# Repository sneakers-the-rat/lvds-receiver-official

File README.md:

# Photodiode LVDS Receiver — 50 Mbps optical receiver module

Replacement for the SiPM-based receiver (Hamamatsu C15522-3010SA module) used for the
optical uplink in Miniscope Zero (Sasatani et al., bioRxiv 2026.09.05.745822).

Design target (set by the customer, not taken from the paper):
- 50 Mbps line rate, 8b/10b coding, 40 Mbps payload, UI = 20 ns
- The paper's mode, as transmitted: Manchester-coded 8 Mbps data (16 Mbaud)
- Optical in (630 nm red / 740 nm NIR channels of the paper), LVDS out (TIA/EIA-644)
- USB-programmable and USB-verifiable from any laptop, no FPGA, no programmer dongle
- Detector: linear-mode Si APD (SiPM rejected: see docs/02-architecture.md)

Status board, stage log and test results: docs/00-status.md
Requirements derived from the paper: docs/01-requirements.md
Architecture and part selection: docs/02-architecture.md
Link budget / noise calculations: sim/link_budget.py (outputs results/link_budget.txt)
Simulations: sim/ (ngspice + Python, each with a pass/fail check)
Firmware: firmware/ (STM32H723 + USB3300 USB-HS, CDC + vendor bulk)
Host tool: host/ (Python, pyusb/serial, PRBS + 8b/10b + Manchester verify)
Hardware: hw/ (KiCad 7 project, generated fabrication outputs in hw/fab/)

Clean-room statement: this design was written from the paper, manufacturer
datasheets (in datasheets/) and first-principles calculations only. No existing
KiCad project was consulted or copied.

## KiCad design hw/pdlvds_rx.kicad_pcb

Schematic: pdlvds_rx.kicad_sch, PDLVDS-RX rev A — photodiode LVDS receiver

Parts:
C1: 0.4pF NP0; C_0402_1005Metric
C2, C3, C7, C8, C9, C10, C11, C13, C14, C16, C19, C23, C26, C27, C30, C47, C48, C50: 100nF; C_0603_1608Metric
C4: 1uF 630V ECWFD2J105JB; ECWFD_1uF_630V
C5, C34: 1nF; C_0603_1608Metric
C6, C25, C35, C37, C51: 10uF; C_0805_2012Metric
C12: 1uF; C_0603_1608Metric
C15: 0.47uF; C_0603_1608Metric
C17, C18: 2.2uF; C_0603_1608Metric
C20: 33pF; C_0402_1005Metric
C21: 33pF; C_0603_1608Metric
C22: 4.7uF; C_0402_1005Metric
C24, C28: 100nF; C_0402_1005Metric
C29: 10nF; C_0603_1608Metric
C31: 4.7uF 10V CL10J475KP8N3NC; C_0603_1608Metric
C32, C33, C52, C53, C54: 100nF 630V; C_1206_3216Metric
C36, C39: 3.3nF; C_0603_1608Metric
C38, C40, C41: 22uF; C_0805_2012Metric
C42, C43, C44, C45, C46, C49: 4.7uF; C_0603_1608Metric
CL1, CL2, CL3, CL4, CL5: Harwin S1001-46R shield clip; HARWIN_S1001
D1: C30737LH-500-90; C30737LH_LCC6
D2: S8664-20K (DNP alt); S8664_TO5
D3: USBLC6-2SC6; SOT-23-6
D4: SMBJ5.0A; D_SMB
D6: LED green PWR; LED_0603_1608Metric
D7: LED green STAT; LED_0603_1608Metric
D8: SMT740 740nm LED BIST source; SMT740_3227
D9: SMBJ5384B 160V OVP DNP (S8664 fit); D_SMB
D10, D11: SMBJ5383B 150V OVP DNP (S8664 fit); D_SMB
D12, D13, D14, D15: ES1J; D_SMA
F1: PTC 1.1A; Fuse_1812_4532Metric
FB1: BLM21PG601SN1D 600R 1.4A; L_0805_2012Metric
FB2: BLM21SP601SN1D 600R 2.3A; L_0805_2012Metric
J1: USB-C receptacle; USB_C_Receptacle_Amphenol_12401610E4-2A
J2: LVDS out 2x3; PinHeader_2x03_P2.54mm_Vertical
J3: SMA test in; SMA_Amphenol_132134_Vertical
J4: SWD 2x5 1.27; PinHeader_2x05_P1.27mm_Vertical
J5: HV enable jumper; PinHeader_1x02_P2.54mm_Vertical
L1: 2.2uH DFE201612E-2R2M=P2 Isat2.4A; L_Murata_DFE201610P
L2: 2.2uH DFE201612E-2R2M=P2; L_Murata_DFE201610P
MH1, MH2, MH3, MH4: M3 corner; MountingHole_3.2mm_M3
MH5, MH6: M2.5 lens holder; MountingHole_2.7mm_M2.5
Q1: IRLML0060TRPBF; SOT-23
R1: 3.3k; R_0603_1608Metric
R2, R10, R44, R45: 1k; R_0603_1608Metric
R3: 806R; R_0603_1608Metric
R4: 200R; R_0603_1608Metric
R5, R6, R12, R15, R16, R22, R23, R37: 10k; R_0603_1608Metric
R7: 0R (fit for TIA direct); R_0603_1608Metric
R8: 0R DNP (fit for post-amp); R_0603_1608Metric
R9: 100k (hysteresis); R_0603_1608Metric
R11: 49.9R DNP; R_0603_1608Metric
R13, R14, R46: 100R; R_0603_1608Metric
R17: 12k 1%; R_0603_1608Metric
R18, R19: 5.1k; R_0603_1608Metric
R20, R21: 4.7k; R_0603_1608Metric
R24: 53.6k (RT, f=250kHz per LT3757 Table 1); R_0603_1608Metric
R25: 143k; R_0603_1608Metric
R26: 33k; R_0603_1608Metric
R27: 10R; R_0603_1608Metric
R28: 0.15R; R_1206_3216Metric
R29: 5.00k HV73V1J (1 of 2); R_0603_1608Metric
R30: 2.35M HV73V2B bleeder (1 of 2); R_1206_3216Metric
R31: 2.94M 0.1% TNPV1210 divider top (1 of 3); R_1210_3225Metric
R32: 75.0k 0.1%; R_0603_1608Metric
R33: 140k 0.1% DAC inject; R_0603_1608Metric
R34: 10M HV73V2B; R_1206_3216Metric
R35: 312k; R_0603_1608Metric
R36, R39: 100k; R_0603_1608Metric
R38: 587k; R_0603_1608Metric
R40: 46k RSET=+4.6V; R_0603_1608Metric
R41, R43: 1k ILIM=125mA; R_0603_1608Metric
R42: 33.2k RSET=+3.32V; R_0603_1608Metric
R47: 5.00k HV73V1J (2 of 2); R_0603_1608Metric
R48: 2.35M HV73V2B bleeder (2 of 2); R_1206_3216Metric
R49: 2.37M 0.1% TNPV1210 divider top (2 of 3); R_1210_3225Metric
R50: 2.37M 0.1% TNPV1210 divider top (3 of 3); R_1210_3225Metric
RJ1, RJ2: 0R DNP; R_0603_1608Metric
SH1: Harwin S02-20150300 20x15x3 can (S1001-46R clips); SHIELD_CAN_S02_20150300
T1: Wurth WE-FLEX HV 749196518 1:5 (N1 pri, N2-N6 sec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; WEFLEXHV_EFD20_12
TP1: HV test point; TestPoint_Pad_D1.5mm
TP2: DBG TX test point; TestPoint_Pad_D1.5mm
TP3: DBG RX test point; TestPoint_Pad_D1.5mm
U1: OPA657N; SOIC-8_3.9x4.9mm_P1.27mm
U2: THS4304DBV; SOT-23-5
U3: LMH7220MK; TSOT-23-6
U4: ADN2813ACPZ; QFN-32-1EP_5x5mm_P0.5mm_EP3.1x3.1mm
U5: SN65LVDS32D; SOIC-16_3.9x9.9mm_P1.27mm
U6: STM32H723ZGT6; LQFP-144_20x20mm_P0.5mm
U7: USB3300-EZK; QFN-32-1EP_5x5mm_P0.5mm_EP3.1x3.1mm
U8: DAC8562SDGS; VSSOP-10_3x3mm_P0.5mm
U9: TMP117NAI; TMP117_WSON6
U10: LT3757EMSE; MSOP-10-1EP_3x3mm_P0.5mm_EP1.68x1.88mm
U11: TPS62130RGT; QFN-16-1EP_3x3mm_P0.5mm_EP1.45x1.45mm
U12: TPS62130RGT (inv); QFN-16-1EP_3x3mm_P0.5mm_EP1.45x1.45mm
U13: LT3042EDD (+VA); DFN-10-1EP_3x3mm_P0.5mm_EP1.55x2.48mm
U14: LT3042EDD (+3V3A); DFN-10-1EP_3x3mm_P0.5mm_EP1.55x2.48mm
X1: 24.000MHz ECS-240-20-5PDN-TR CL20; Crystal_SMD_HC49-SD
X2: ASE-25.000MHZ-L-R-T 3.3V CMOS OSC; Oscillator_SMD_Abracon_ASE-4Pin_3.2x2.5mm

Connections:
+3V3A: C24.1, C46.1, C49.1, U6.32 (VREF+), U6.33 (VDDA), U7.6 (VDD3.3), U7.16 (VDD3.3), U7.25 (VDD3.3), U7.30 (VDD3.3), U7.31 (REG_EN), U9.5 (V+), U14.9 (OUTS), U14.10 (OUT)
+3V3D: C16.1, C27.1, C28.1, C38.1, C47.1, C48.1, D6.2 (A), FB1.1, J4.1 (VTREF), L1.2, R15.2, R20.2, R21.2, R22.2, R35.1, R37.2, R45.1, R46.1, U5.4 (G), U5.10 (3A), U5.14 (4A), U5.16 (VCC), U6.6 (VBAT), U6.17 (VDD), U6.30 (VDD), U6.39 (VDD), U6.52 (VDD), U6.62 (VDD), U6.72 (VDD), U6.84 (VDD), U6.108 (VDD), U6.121 (VDD), U6.131 (VDD), U6.143 (PDR_ON), U6.144 (VDD), U8.5 (CLR), U8.9 (AVDD), U11.14 (VOS), X2.1 (OE), X2.4 (VCC)
+3V3D_CDR: C50.1, C51.1, FB1.2, U4.1 (VCC), U4.2 (VCC), U4.12 (VCC), U4.18 (VCC), U4.24 (VCC), U4.31 (VCC), U4.32 (VCC)
+5V: C25.1, C35.1, C37.1, C43.1, D3.5 (VBUS), D4.1 (K), F1.2, R25.1, T1.1 (PRI_A), U7.4 (VBUS), U10.10 (VIN), U11.10 (AVIN), U11.11 (PVIN), U11.12 (PVIN), U11.13 (EN), U12.10 (AVIN), U12.11 (PVIN), U12.12 (PVIN), U12.13 (EN), U13.1 (IN), U13.2 (IN), U13.3 (EN/UV), U13.6 (PGFB), U14.1 (IN), U14.2 (IN), U14.3 (EN/UV), U14.6 (PGFB)
+VA: C2.1, C7.1, C10.1, C44.1, R5.1, U1.7 (V+), U2.5 (VS+), U3.5 (VCC), U13.9 (OUTS), U13.10 (OUT)
-VA: C3.1, C41.1, FB2.2, U1.4 (V-)
APD_A: C1.2, D1.1 (ANODE), D1.2 (ANODE), D1.3 (ANODE), D1.4 (ANODE), D1.6 (ANODE), R1.2, RJ1.2, U1.2 (-IN)
APD_A_ALT: D2.1 (LEAD_A), RJ1.1
APD_K: C4.1, C33.1, D1.5 (CATHODE), R30.1, R31.1, R34.1, R47.2, RJ2.2
APD_K_ALT: D2.2 (LEAD_K), RJ2.1
BIST_A: D8.2 (A), R46.2
BIST_DRV: D8.1 (K), U6.98 (PC8)
BOOT0: R16.1, U6.138 (BOOT0)
CAP_CLK: U5.5 (2Y), U6.34 (PA0)
CAP_DATA: U5.3 (1Y), U6.35 (PA1)
CC1: J1.A5 (CC1), R18.1
CC2: J1.B5 (CC2), R19.1
CDR_CLKN: J2.6 (CLKN), R14.2, U4.25 (CLKOUTN), U5.7 (2B)
CDR_CLKP: J2.5 (CLKP), R14.1, U4.26 (CLKOUTP), U5.6 (2A)
CDR_DATN: J2.2 (DATN), R13.2, U4.28 (DATAOUTN), U5.1 (1B)
CDR_DATP: J2.1 (DATP), R13.1, U4.29 (DATAOUTP), U5.2 (1A)
CDR_LOL: U4.16 (LOL), U6.36 (PA2)
CDR_LOS: U4.22 (LOS), U6.75 (PB14)
CDR_NIN: C9.2, U4.4 (NIN)
CDR_PIN: C8.2, U4.5 (PIN)
CDR_SQUELCH: U4.27 (SQUELCH), U6.76 (PB15)
CDR_VREF: C12.1, U4.3 (VREF)
CF1: C15.1, U4.15 (CF1)
CF2: C15.2, U4.14 (CF2)
CMP_IN: R7.2, R8.2, R9.2, R11.2, U3.6 (IN+)
CMP_QN: C9.1, U3.3 (Qn)
CMP_QP: C8.1, R9.1, U3.4 (Q)
DAC_SYNC: U6.110 (PA15(JTDI)), U8.6 (SYNC)
DAC_VREF: C26.1, U8.10 (VREF)
DBG_RX: TP3.1, U6.102 (PA10)
DBG_TX: TP2.1, U6.101 (PA9)
DM_CON: D3.3 (IO2), J1.A7 (DN), J1.B7 (DN)
DM_PHY: D3.4 (IO2p), U7.8 (DM)
DP_CON: D3.1 (IO1), J1.A6 (DP), J1.B6 (DP)
DP_PHY: D3.6 (IO1p), U7.7 (DP)
FB_3V3: R35.2, R36.1, U11.5 (FB)
FB_NEG: R38.2, R39.1, U12.5 (FB)
FLY_PRI: Q1.3 (D), T1.2 (PRI_B)
GND: C2.2, C3.2, C4.2, C6.2, C7.2, C10.2, C11.2, C12.2, C14.2, C16.2, C17.2, C18.2, C19.2, C20.2, C21.2, C22.2, C23.2, C24.2, C25.2, C26.2, C27.2, C28.2, C29.2, C30.2, C31.2, C32.2, C33.2, C34.2, C35.2, C36.2, C37.2, C38.2, C40.1, C41.2, C42.2, C43.2, C44.2, C45.2, C46.2, C47.2, C48.2, C49.2, C50.2, C51.2, C53.2, CL1.1, CL1.2, CL1.3, CL2.1, CL2.2, CL2.3, CL3.1, CL3.2, CL3.3, CL4.1, CL4.2, CL4.3, CL5.1, CL5.2, CL5.3, D2.3 (CASE), D3.2 (GND), D4.2 (A), D11.2 (A), D12.2 (A), J1.A1 (GND), J1.A12 (GND), J1.B1 (GND), J1.B12 (GND), J1.SH (SHIELD), J2.3 (GND), J2.4 (GND), J3.2 (SH), J3.3 (SH), J3.4 (SH), J3.5 (SH), J4.3 (GND), J4.5 (GND), J4.7 (GND), J4.9 (GND), MH1.1, MH2.1, MH3.1, MH4.1, R6.2, R12.2, R16.2, R17.2, R18.2, R19.2, R24.2, R26.2, R28.2, R32.2, R36.2, R38.1, R40.2, R41.2, R42.2, R43.2, R44.2, R48.2, T1.3 (SEC_GND), U1.3 (+IN), U2.2 (VS-), U3.2 (GND), U4.8 (VEE), U4.13 (VEE), U4.17 (VEE), U4.19 (SADDR5), U4.23 (VEE), U4.30 (VEE), U4.33 (EP), U5.8 (GND), U5.9 (3B), U5.12 (Gn), U5.15 (4B), U6.16 (VSS), U6.31 (VSSA), U6.38 (VSS), U6.51 (VSS), U6.61 (VSS), U6.83 (VSS), U6.94 (VSS), U6.107 (VSS), U6.120 (VSS), U6.130 (VSS), U7.1 (GND), U7.2 (GND), U7.5 (ID), U7.10 (EXTVBUS), U7.33 (EP), U8.3 (GND), U8.4 (LDAC), U9.2 (GND), U9.4 (ADD0), U9.7 (EP), U10.5 (SYNC), U10.11 (EP), U11.6 (AGND), U11.7 (FSW), U11.8 (DEF), U11.15 (PGND), U11.16 (PGND), U11.17 (EP), U13.8 (GND), U13.11 (EP), U14.8 (GND), U14.11 (EP), X2.2 (GND)
HV_DAC: R33.1, U8.2 (VOUTB)
HV_EN: J5.1 (EN), U6.97 (PC7)
HV_FBX: C34.1, R32.1, R33.2, R50.2, U10.2 (FBX)
HV_GATE: R27.1, U10.7 (GATE)
HV_INTVCC: C31.1, U10.8 (INTVCC)
HV_M1: C52.2, C54.1, D12.1 (K), D13.2 (A)
HV_M2: C53.1, D13.1 (K), D14.2 (A)
HV_M3: C54.2, D14.1 (K), D15.2 (A)
HV_OVP1: D9.2 (A), D10.1 (K)
HV_OVP2: D10.2 (A), D11.1 (K)
HV_R29M: R29.2, R47.1
HV_R30M: R30.2, R48.1
HV_R31A: R31.2, R49.1
HV_R31B: R49.2, R50.1
HV_RAW: C32.1, D9.1 (K), D15.1 (K), R29.1
HV_RT: R24.1, U10.4 (RT)
HV_S1: T1.4 (S1), T1.5 (S1B)
HV_S2: T1.6 (S2), T1.12 (S2B)
HV_S3: T1.10 (S3B), T1.11 (S3)
HV_S4: T1.8 (S4B), T1.9 (S4)
HV_SEC: C52.1, T1.7 (SEC_A)
HV_SENSE: Q1.2 (S), R28.1, U10.6 (SENSE)
HV_SHDN: J5.2 (SHDN), R25.2, R26.1, U6.42 (PA6), U10.9 (SHDN/UVLO)
HV_SS: C30.1, U10.3 (SS)
HV_VC: R23.1, U10.1 (VC)
HV_VC2: C29.1, R23.2
I2C_SCL: R20.1, U4.20 (SCK), U6.136 (PB6), U9.1 (SCL)
I2C_SDA: R21.1, U4.21 (SDA), U6.137 (PB7), U9.6 (SDA)
ILIM_A: R43.1, U14.5 (ILIM)
ILIM_P: R41.1, U13.5 (ILIM)
LED_PWR_K: D6.1 (K), R44.1
LED_STAT: D7.1 (K), U6.99 (PC9)
LED_STAT_A: D7.2 (A), R45.2
MOS_G: Q1.1 (G), R27.2
NEG_RAW: C39.2, C40.2, FB2.1, L2.2, R39.2, U12.6 (AGND), U12.7 (FSW), U12.8 (DEF), U12.14 (VOS), U12.15 (PGND), U12.16 (PGND), U12.17 (EP)
NRST: C19.1, J4.10 (NRST), R15.1, U6.25 (NRST)
PG_3V3: R37.1, U6.140 (PB9), U11.4 (PG)
PHY_1V8: C22.1, U7.15 (VDD1.8), U7.26 (VDD1.8)
PHY_1V8A: C23.1, U7.29 (VDDA1.8)
POST_INN: R3.2, R4.1, U2.4 (IN-)
POST_INP: C5.2, R2.1, U2.3 (IN+)
POST_OUT: R3.1, R8.1, U2.1 (VOUT)
RBIAS: R17.1, U7.32 (RBIAS)
REFCLK: U4.10 (REFCLKP), X2.3 (OUT)
REFCLKN: C14.1, U4.11 (REFCLKN)
SET_A: C45.1, R42.1, U14.7 (SET)
SET_P: C42.1, R40.1, U13.7 (SET)
SLICEN: C13.2, U4.7 (SLICEN)
SLICEP: C13.1, U4.6 (SLICEP)
SPI_MOSI: U6.113 (PC12), U8.8 (DIN)
SPI_SCK: U6.111 (PC10), U8.7 (SCLK)
SS_3V3: C36.1, U11.9 (SS/TR)
SS_NEG: C39.1, U12.9 (SS/TR)
SW1: L1.1, U11.1 (SW), U11.2 (SW), U11.3 (SW)
SW2: L2.1, U12.1 (SW), U12.2 (SW), U12.3 (SW)
SWCLK: J4.4 (SWCLK), U6.109 (PA14(JTCK)
SWDIO: J4.2 (SWDIO), U6.105 (PA13(JTMS)
TEST_IN: J3.1 (SIG), R11.1
THRADJ: R12.1, U4.9 (THRADJ)
THR_DAC: R10.1, U8.1 (VOUTA)
THR_FILT: C11.1, R10.2, U3.1 (IN-)
TIA_OUT: C1.1, C5.1, R1.1, R7.1, U1.6 (OUT)
TMP_ALERT: R22.1, U6.139 (PB8), U9.3 (ALERT)
TP_HV: R34.2, TP1.1
ULPI_CK: U6.41 (PA5), U7.14 (CLKOUT)
ULPI_D0: U6.37 (PA3), U7.24 (DATA0)
ULPI_D1: U6.46 (PB0), U7.23 (DATA1)
ULPI_D2: U6.47 (PB1), U7.22 (DATA2)
ULPI_D3: U6.69 (PB10), U7.21 (DATA3)
ULPI_D4: U6.70 (PB11), U7.20 (DATA4)
ULPI_D5: U6.73 (PB12), U7.19 (DATA5)
ULPI_D6: U6.74 (PB13), U7.18 (DATA6)
ULPI_D7: U6.135 (PB5), U7.17 (DATA7)
ULPI_DIR: U6.28 (PC2_C), U7.12 (DIR)
ULPI_NXT: U6.29 (PC3_C), U7.11 (NXT)
ULPI_STP: U6.26 (PC0), U7.13 (STP)
USB_RST: U6.40 (PA4), U7.9 (RESET)
VBUS_RAW: F1.1, J1.A4 (VBUS), J1.A9 (VBUS), J1.B4 (VBUS), J1.B9 (VBUS)
VCAP1: C17.1, U6.106 (VCAP)
VCAP2: C18.1, U6.71 (VCAP)
VMID: C6.1, R2.2, R4.2, R5.2, R6.1
XI: C20.1, U7.28 (XI), X1.1 (XI)
XO: C21.1, U7.27 (XO), X1.2 (XO)

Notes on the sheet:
ANALOG FRONT END - APD / TIA / COMPARATOR
HV BIAS - LT3757 FLYBACK
POWER - BUCKS + LDOs
CLOCK + DATA RECOVERY - ADN2813
MCU - STM32H723
USB - USB3300 PHY + USB-C
MECHANICAL
LVDS -> CMOS CAPTURE + LVDS OUTPUT
DAC + TEMPERATURE - DAC8562 / TMP117
LEDS / MISC

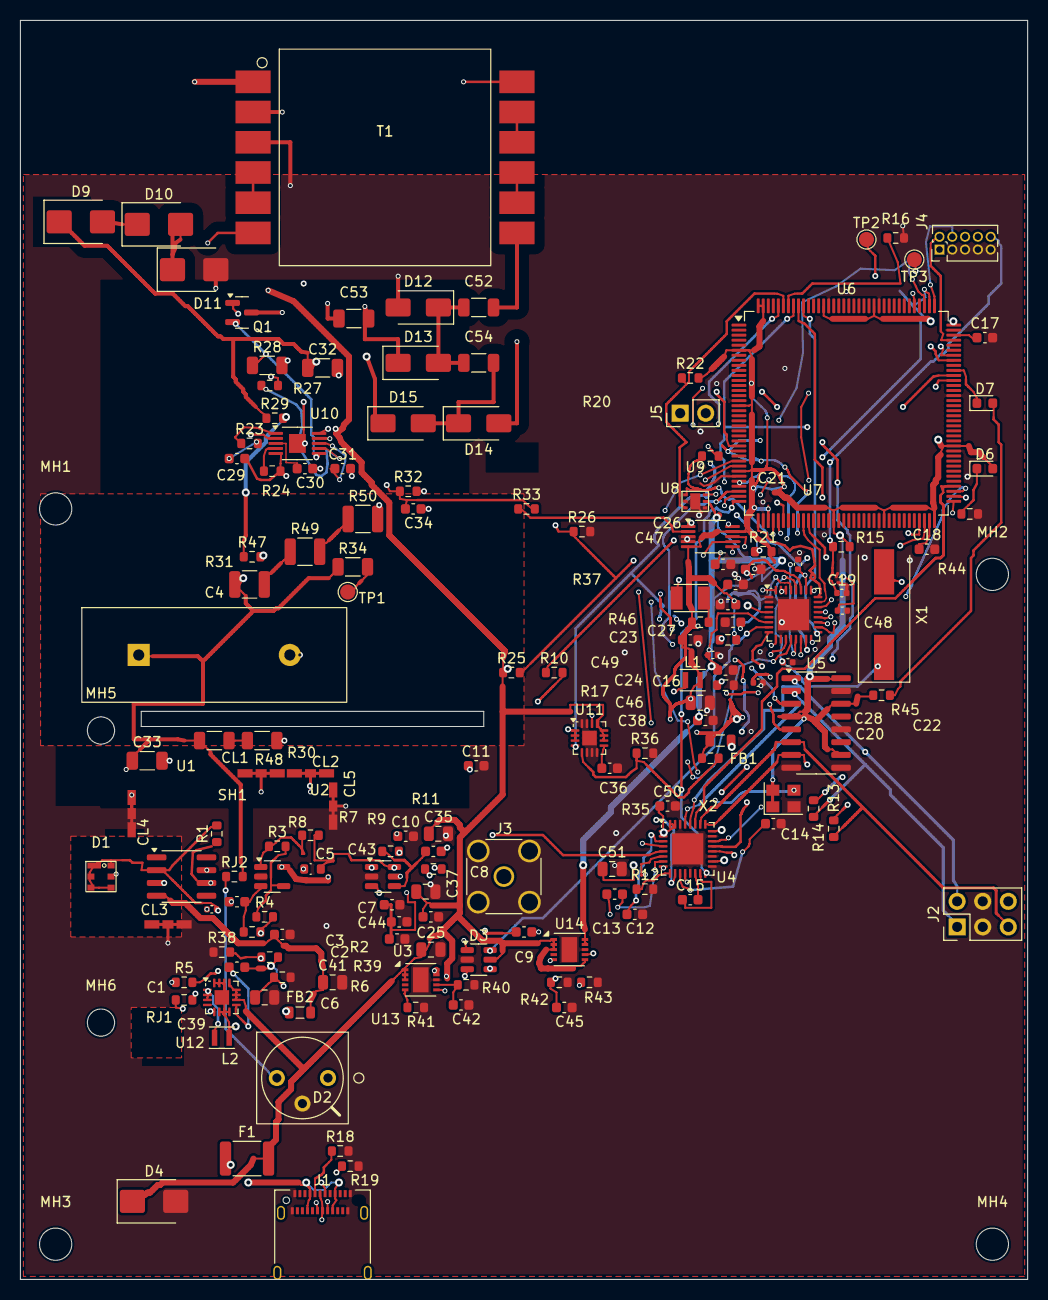
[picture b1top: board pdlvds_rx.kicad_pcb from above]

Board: 4 copper layers, 100.0 x 125.0 mm, 163 parts (1 on the bottom side), 127 nets.

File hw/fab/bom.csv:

Refs,Qty,Value,Footprint
C1,1,0.4pF NP0,Capacitor_SMD:C_0402_1005Metric
C15,1,0.47uF,Capacitor_SMD:C_0603_1608Metric
C17 C18,2,2.2uF,Capacitor_SMD:C_0603_1608Metric
C2 C3 C7 C8 C9 C10 C11 C13 C14 C16 C19 C23 C24 C26 C27 C28 C30 C47 C48 C50,20,100nF,Capacitor_SMD:C_0603_1608Metric
C20 C21,2,18pF,Capacitor_SMD:C_0603_1608Metric
C22 C31 C42 C43 C44 C45 C46 C49,8,4.7uF,Capacitor_SMD:C_0603_1608Metric
C29,1,10nF,Capacitor_SMD:C_0603_1608Metric
C32 C33,2,100nF 630V,Capacitor_SMD:C_1206_3216Metric
C36 C39,2,3.3nF,Capacitor_SMD:C_0603_1608Metric
C38 C40 C41,3,22uF,Capacitor_SMD:C_0805_2012Metric
C4 C12,2,1uF,Capacitor_SMD:C_0603_1608Metric
C5 C34,2,1nF,Capacitor_SMD:C_0603_1608Metric
C6 C25 C35 C37 C51,5,10uF,Capacitor_SMD:C_0805_2012Metric
D1,1,C30737LH-500-90,pdlvds:C30737LH_LCC6
D2,1,S8664-20K (DNP alt),pdlvds:S8664_TO5
D3,1,USBLC6-2SC6,Package_TO_SOT_SMD:SOT-23-6
D4,1,SMBJ5.0A,Diode_SMD:D_SMA
D5,1,ES1J,Diode_SMD:D_SMA
D6,1,LED green PWR,LED_SMD:LED_0603_1608Metric
D7,1,LED green STAT,LED_SMD:LED_0603_1608Metric
D8,1,LED 740nm BIST source,LED_SMD:LED_1206_3216Metric
F1,1,PTC 1.1A,Fuse:Fuse_1812_4532Metric
FB1 FB2,2,600R@100MHz,Inductor_SMD:L_0805_2012Metric
J1,1,USB-C receptacle,Connector_USB:USB_C_Receptacle_Amphenol_12401610E4-2A
J2,1,LVDS out 2x3,Connector_PinHeader_2.54mm:PinHeader_2x03_P2.54mm_Vertical
J3,1,SMA test in,Connector_Coaxial:SMA_Amphenol_132134_Vertical
J4,1,SWD 2x5 1.27,Connector_PinHeader_1.27mm:PinHeader_2x05_P1.27mm_Vertical
J5,1,HV enable jumper,Connector_PinHeader_2.54mm:PinHeader_1x02_P2.54mm_Vertical
L1 L2,2,2.2uH,Inductor_SMD:L_0805_2012Metric
MH1 MH2 MH3 MH4,4,M3 corner,MountingHole:MountingHole_3.2mm_M3
MH5 MH6,2,M2.5 lens holder,MountingHole:MountingHole_2.7mm_M2.5
Q1,1,IRLML0030 SOT-23,Package_TO_SOT_SMD:SOT-23
R1,1,3.3k,Resistor_SMD:R_0603_1608Metric
R11,1,49.9R DNP,Resistor_SMD:R_0603_1608Metric
R13 R14 R46,3,100R,Resistor_SMD:R_0603_1608Metric
R17,1,12k 1%,Resistor_SMD:R_0603_1608Metric
R18 R19,2,5.1k,Resistor_SMD:R_0603_1608Metric
R2 R10 R44 R45,4,1k,Resistor_SMD:R_0603_1608Metric
R20 R21,2,4.7k,Resistor_SMD:R_0603_1608Metric
R24,1,"24.9k (RT, VERIFY f=250k)",Resistor_SMD:R_0603_1608Metric
R25,1,143k,Resistor_SMD:R_0603_1608Metric
R26,1,33k,Resistor_SMD:R_0603_1608Metric
R28,1,0.05R,Resistor_SMD:R_1206_3216Metric
R29,1,10k HV,Resistor_SMD:R_1206_3216Metric
R3,1,806R,Resistor_SMD:R_0603_1608Metric
R30,1,4.7M bleeder,Resistor_SMD:R_1206_3216Metric
R31,1,7.68M 0.1% HV divider top,Resistor_SMD:R_1206_3216Metric
R32,1,75.0k 0.1%,Resistor_SMD:R_0603_1608Metric
R33,1,140k 0.1% DAC inject,Resistor_SMD:R_0603_1608Metric
R34,1,10M HV probe,Resistor_SMD:R_1206_3216Metric
R35,1,312k,Resistor_SMD:R_0603_1608Metric
R36 R39,2,100k,Resistor_SMD:R_0603_1608Metric
R38,1,587k,Resistor_SMD:R_0603_1608Metric
R4,1,200R,Resistor_SMD:R_0603_1608Metric
R40,1,46k RSET=+4.6V,Resistor_SMD:R_0603_1608Metric
R41 R43,2,1k ILIM=125mA,Resistor_SMD:R_0603_1608Metric
R42,1,33.2k RSET=+3.32V,Resistor_SMD:R_0603_1608Metric
R5 R6 R12 R15 R16 R22 R23 R27 R37,9,10k,Resistor_SMD:R_0603_1608Metric
R7,1,0R (fit for TIA direct),Resistor_SMD:R_0603_1608Metric
R8,1,0R DNP (fit for post-amp),Resistor_SMD:R_0603_1608Metric
R9,1,100k (hysteresis),Resistor_SMD:R_0603_1608Metric
RJ1 RJ2,2,0R DNP,Resistor_SMD:R_0603_1608Metric
SH1,1,Shield can frontend,pdlvds:SHIELD_CAN_26x20
T1,1,Flyback xfmr 1:20,pdlvds:XFMR_FLYBACK_6P
TP1,1,HV test point,TestPoint:TestPoint_Pad_D1.5mm
TP2,1,DBG TX test point,TestPoint:TestPoint_Pad_D1.5mm
TP3,1,DBG RX test point,TestPoint:TestPoint_Pad_D1.5mm
U1,1,OPA657N,Package_SO:SOIC-8_3.9x4.9mm_P1.27mm
U10,1,LT3757EMSE,Package_SO:MSOP-10-1EP_3x3mm_P0.5mm_EP1.68x1.88mm
U11,1,TPS62130RGT,Package_DFN_QFN:QFN-16-1EP_3x3mm_P0.5mm_EP1.45x1.45mm
U12,1,TPS62130RGT (inv),Package_DFN_QFN:QFN-16-1EP_3x3mm_P0.5mm_EP1.45x1.45mm
U13,1,LT3042EDD (+VA),Package_DFN_QFN:DFN-10-1EP_3x3mm_P0.5mm_EP1.55x2.48mm
U14,1,LT3042EDD (+3V3A),Package_DFN_QFN:DFN-10-1EP_3x3mm_P0.5mm_EP1.55x2.48mm
U2,1,THS4304DBV,Package_TO_SOT_SMD:SOT-23-5
U3,1,LMH7220MK,Package_TO_SOT_SMD:TSOT-23-6
U4,1,ADN2813ACPZ,Package_DFN_QFN:QFN-32-1EP_5x5mm_P0.5mm_EP3.1x3.1mm
U5,1,SN65LVDS32D,Package_SO:SOIC-16_3.9x9.9mm_P1.27mm
U6,1,STM32H723ZGT6,Package_QFP:LQFP-144_20x20mm_P0.5mm
U7,1,USB3300-EZK,Package_DFN_QFN:QFN-32-1EP_5x5mm_P0.5mm_EP3.1x3.1mm
U8,1,DAC8562SDGS,Package_SO:VSSOP-10_3x3mm_P0.5mm
U9,1,TMP117NAI,pdlvds:TMP117_WSON6
X1,1,24MHz,Crystal:Crystal_SMD_3225-4Pin_3.2x2.5mm
X2,1,25MHz OSC,Oscillator:Oscillator_SMD_Abracon_ASE-4Pin_3.2x2.5mm

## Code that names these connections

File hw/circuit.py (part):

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    "3":("Qn","out","CMP_QN"), "4":("Q","out","CMP_QP"),
    "5":("VCC","pwr_in","+VA"), "6":("IN+","in","CMP_IN")}, "afe"),
 P("R9","100k (hysteresis)", R0603, "R", {"1":("","passive","CMP_QP"), "2":("","passive","CMP_IN")}, "afe"),
 P("C8","100nF", C0603, "C", {"1":("","passive","CMP_QP"), "2":("","passive","CDR_PIN")}, "afe"),
 P("C9","100nF", C0603, "C", {"1":("","passive","CMP_QN"), "2":("","passive","CDR_NIN")}, "afe"),
 P("C10","100nF", C0603, "C", {"1":("","passive","+VA"), "2":("","passive","GND")}, "afe"),
 P("R10","1k", R0603, "R", {"1":("","passive","THR_DAC"), "2":("","passive","THR_FILT")}, "afe"),
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 P("U4","ADN2813ACPZ", ("Package_DFN_QFN","QFN-32-1EP_5x5mm_P0.5mm_EP3.1x3.1mm"), "box",
   {"1":("VCC","pwr_in","+3V3D_CDR"), "2":("VCC","pwr_in","+3V3D_CDR"),
    "3":("VREF","passive","CDR_VREF"), "4":("NIN","in","CDR_NIN"),
    "5":("PIN","in","CDR_PIN"), "6":("SLICEP","passive","SLICEP"),
    "7":("SLICEN","passive","SLICEN"), "8":("VEE","pwr_in","GND"),
    "9":("THRADJ","passive","THRADJ"), "10":("REFCLKP","in","REFCLK"),
    "11":("REFCLKN","in","REFCLKN"), "12":("VCC","pwr_in","+3V3D_CDR"),
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 P("C16","100nF", C0603, "C", {"1":("","passive","+3V3D"), "2":("","passive","GND")}, "cap"),
 # ---------------- MCU (pins keyed by NAME; numbers resolved from KiCad lib) ----
 P("U6","STM32H723ZGT6", ("Package_QFP","LQFP-144_20x20mm_P0.5mm"), "stm32",
   {"PA3":"ULPI_D0","PB0":"ULPI_D1","PB1":"ULPI_D2","PB10":"ULPI_D3",
    "PB11":"ULPI_D4","PB12":"ULPI_D5","PB13":"ULPI_D6","PB5":"ULPI_D7",
    "PA5":"ULPI_CK","PC0":"ULPI_STP","PC2_C":"ULPI_DIR","PC3_C":"ULPI_NXT",
    "PA13":"SWDIO","PA14":"SWCLK","PB6":"I2C_SCL","PB7":"I2C_SDA",
    "PC10":"SPI_SCK","PC12":"SPI_MOSI","PA15":"DAC_SYNC",
    "PA0":"CAP_CLK","PA1":"CAP_DATA","PA2":"CDR_LOL","PB14":"CDR_LOS",
    "PB15":"CDR_SQUELCH","PC7":"HV_EN","PC8":"BIST_DRV","PC9":"LED_STAT",
    "PB8":"TMP_ALERT","PB9":"PG_3V3","PA4":"USB_RST",
    "PA9":"DBG_TX","PA10":"DBG_RX","PA6":"HV_SHDN"}, "mcu"),
 P("C17","2.2uF", C0603, "C", {"1":("","passive","VCAP1"), "2":("","passive","GND")}, "mcu"),
 P("C18","2.2uF", C0603, "C", {"1":("","passive","VCAP2"), "2":("","passive","GND")}, "mcu"),
 P("R15","10k", R0603, "R", {"1":("","passive","NRST"), "2":("","passive","+3V3D")}, "mcu"),
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 P("R28","0.15R", R1206, "R", {"1":("","passive","HV_SENSE"), "2":("","passive","GND")}, "hv"),
 # T1: Wurth WE-FLEX HV 749196518 catalog transformer (docs/11, docs/12).
 # N1 (1 dot / 2) = primary; N2..N6 in series = secondary (1:5), string
 # dot-end (pin 3) at GND, far end (pin 7) = HV_SEC. Two-cell
 # Cockcroft-Walton ladder (D12-D15, C52-C54) replaces the old single
 # rectifier D5; R28 0.15R caps the LT3757 peak at <=0.80 A, below the
 # part's 0.93 A saturation figure (proof: sim/check_hv_flex.py).
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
